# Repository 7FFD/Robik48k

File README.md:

# Robik48k

One of my collegues has sent to me ZX Robik, one of the ZX Spectrum clones created in SU.
During restoration, I've collected some artifacts that can be useful.

## AV-board-robik

The schematic of video output cascade to isolate logic from TV Set (SCART).
Indeed, Robik doen't have such cascade that in some cases leads to burning KP556PT2.
This schematic was borrowed from Harlequin.

## LM2596

Replacement of 7805 voltage regulator with more efficient based on LM2596.

## Robik2ZXBusAdapter

In order to connect ZX Spectrum pereferial to Robik an adapter has been created.
Besides that few changes on Robik must be applied, see Robik_Nick+fixed_by_Maksym_7FFD:
1. Make ROMCS signal working by adding 560 omh resistors
2. Add KJOYCS signal and connect to system connector
3. Fix /WAIT signal to work on input
4. Add +12V to system connector

## W27C512toKP556PT2

Since KP556PT2 is quite old IC with low reliability it's much better to replace with EEPROM W27C512-50.
Both D26/D27 can be replaced, use /xxxrom-dump/robik-plm-012-01-D26.bin for video output PLM and /xxxrom-dump/robik-plm-012-D27.bin for system PLM.

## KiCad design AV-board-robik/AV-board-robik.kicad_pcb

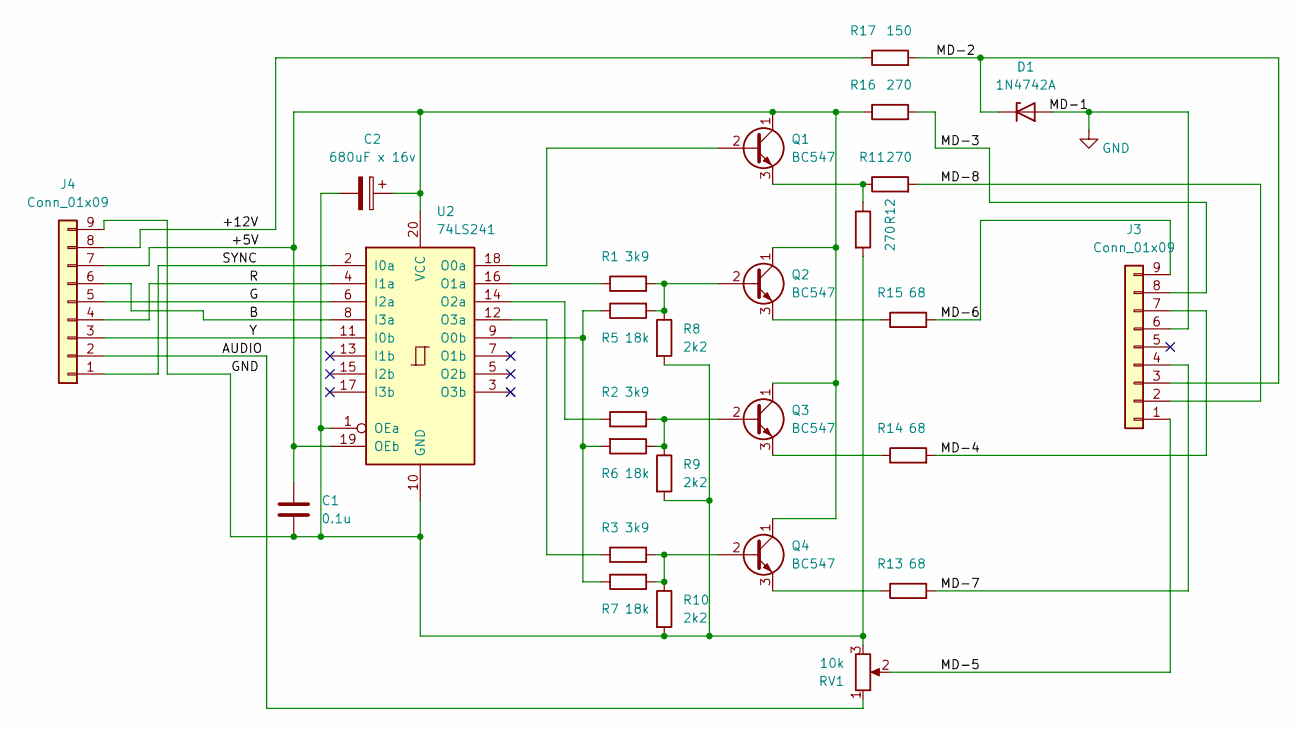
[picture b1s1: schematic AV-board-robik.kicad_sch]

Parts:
C1: 0.1u; C_Disc_D4.3mm_W1.9mm_P5.00mm
C2: 680uF x 16v; CP_Radial_D5.0mm_P2.50mm
D1: 1N4742A; D_DO-41_SOD81_P10.16mm_Horizontal
J3, J4: Conn_01x09; PinHeader_1x09_P2.54mm_Horizontal
Q1, Q2, Q3, Q4: BC547; TO-92_Inline
R1, R2, R3: 3k9; R_Axial_DIN0204_L3.6mm_D1.6mm_P5.08mm_Horizontal
R5, R6, R7: 18k; R_Axial_DIN0204_L3.6mm_D1.6mm_P5.08mm_Horizontal
R8, R9, R10: 2k2; R_Axial_DIN0204_L3.6mm_D1.6mm_P5.08mm_Horizontal
R11, R12, R16: 270; R_Axial_DIN0204_L3.6mm_D1.6mm_P5.08mm_Horizontal
R13, R14, R15: 68; R_Axial_DIN0204_L3.6mm_D1.6mm_P5.08mm_Horizontal
R17: 150; R_Axial_DIN0204_L3.6mm_D1.6mm_P5.08mm_Horizontal
RV1: 10k; Potentiometer_Piher_PT-6-V_Vertical
U2: 74LS241; DIP-20_W7.62mm_LongPads

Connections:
/+5V: C1.1, C2.1, J4.7, Q1.1 (C), Q2.1 (C), Q3.1 (C), Q4.1 (C), R16.1, U2.19 (OEb), U2.20 (VCC)
/+12V: J4.8, R17.1
/AUDIO: J4.2, RV1.1
/B: J4.6, U2.8 (I3a)
/G: J4.5, U2.6 (I2a)
/MD-2: D1.1 (K), J3.3, R17.2
/MD-3: J3.8, R16.2
/MD-4: J3.7, R14.2
/MD-5: J3.1, RV1.2
/MD-6: J3.9, R15.2
/MD-7: J3.4, R13.2
/MD-8: J3.2, R11.2
/R: J4.4, U2.4 (I1a)
/SYNC: J4.1, U2.2 (I0a)
/Y: J4.3, U2.11 (I0b)
GND: C1.2, C2.2, D1.2 (A), J3.6, J4.9, R8.2, R9.2, R10.2, R12.2, RV1.3, U2.1 (OEa), U2.10 (GND)
unnamed: Q1.2 (B), U2.18 (O0a)
unnamed: Q1.3 (E), R11.1, R12.1
unnamed: Q2.2 (B), R1.2, R5.2, R8.1
unnamed: Q2.3 (E), R15.1
unnamed: Q3.2 (B), R2.2, R6.1, R9.1
unnamed: Q3.3 (E), R14.1
unnamed: Q4.2 (B), R3.2, R7.2, R10.1
unnamed: Q4.3 (E), R13.1
unnamed: R5.1, R6.2, R7.1, U2.9 (O0b)
unnamed: R1.1, U2.16 (O1a)
unnamed: R2.1, U2.14 (O2a)
unnamed: R3.1, U2.12 (O3a)

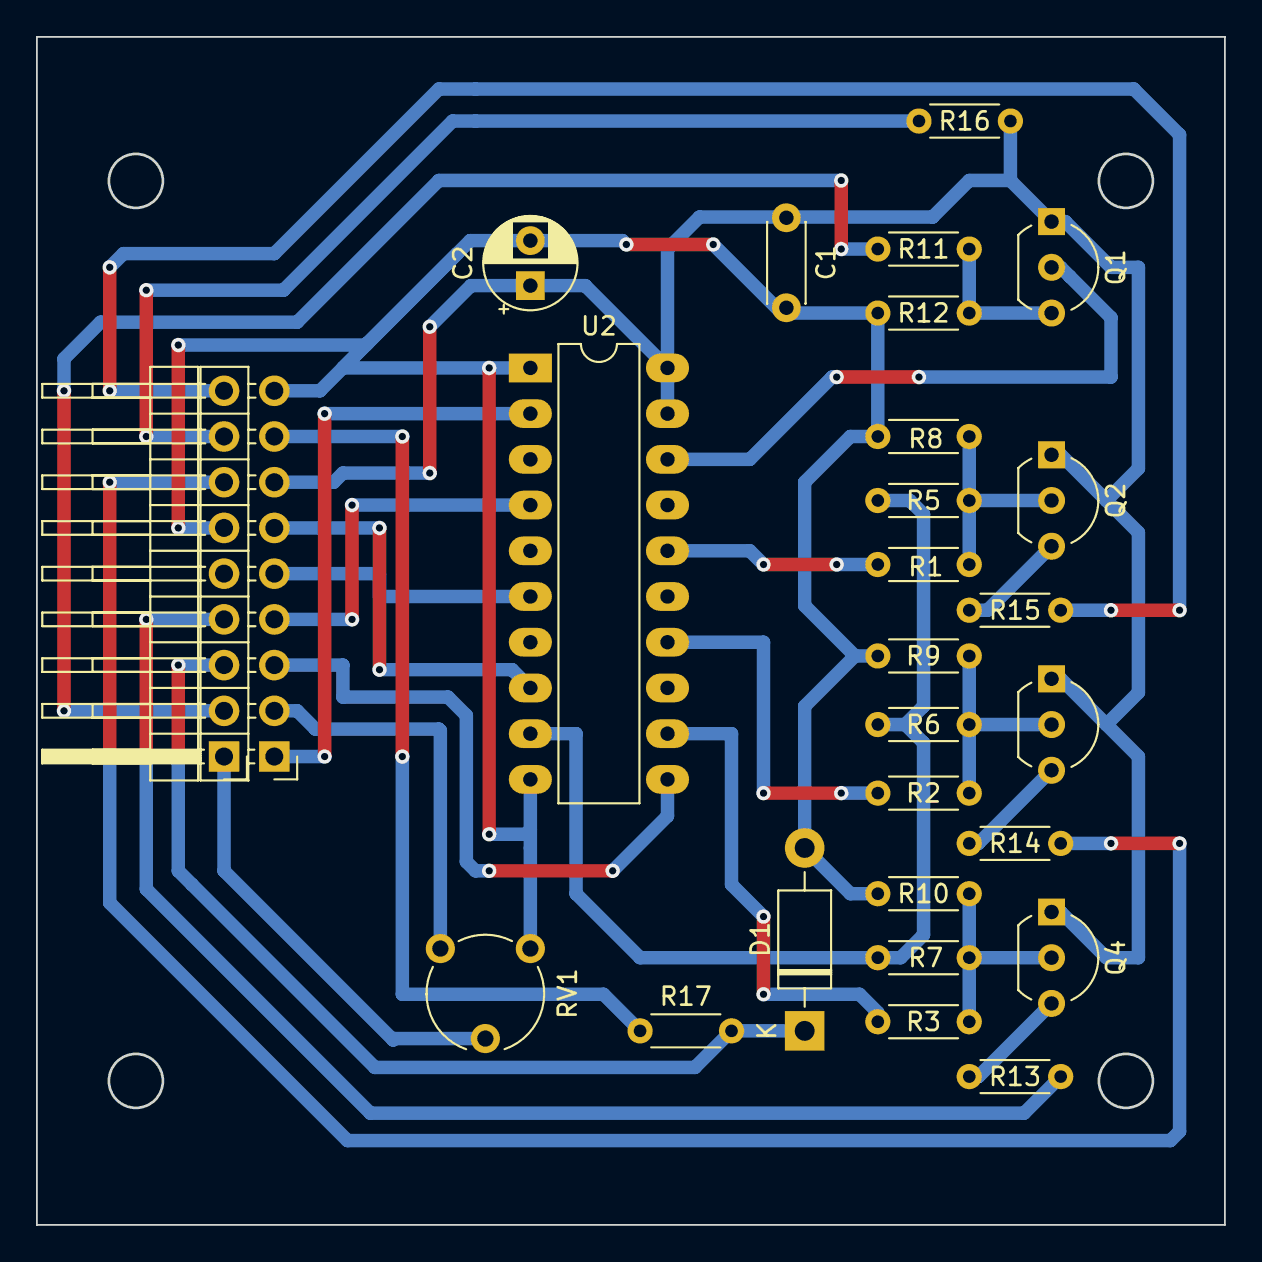
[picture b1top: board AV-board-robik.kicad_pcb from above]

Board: 2 copper layers, 66.0 x 66.0 mm, 27 parts (0 on the bottom side), 28 nets.

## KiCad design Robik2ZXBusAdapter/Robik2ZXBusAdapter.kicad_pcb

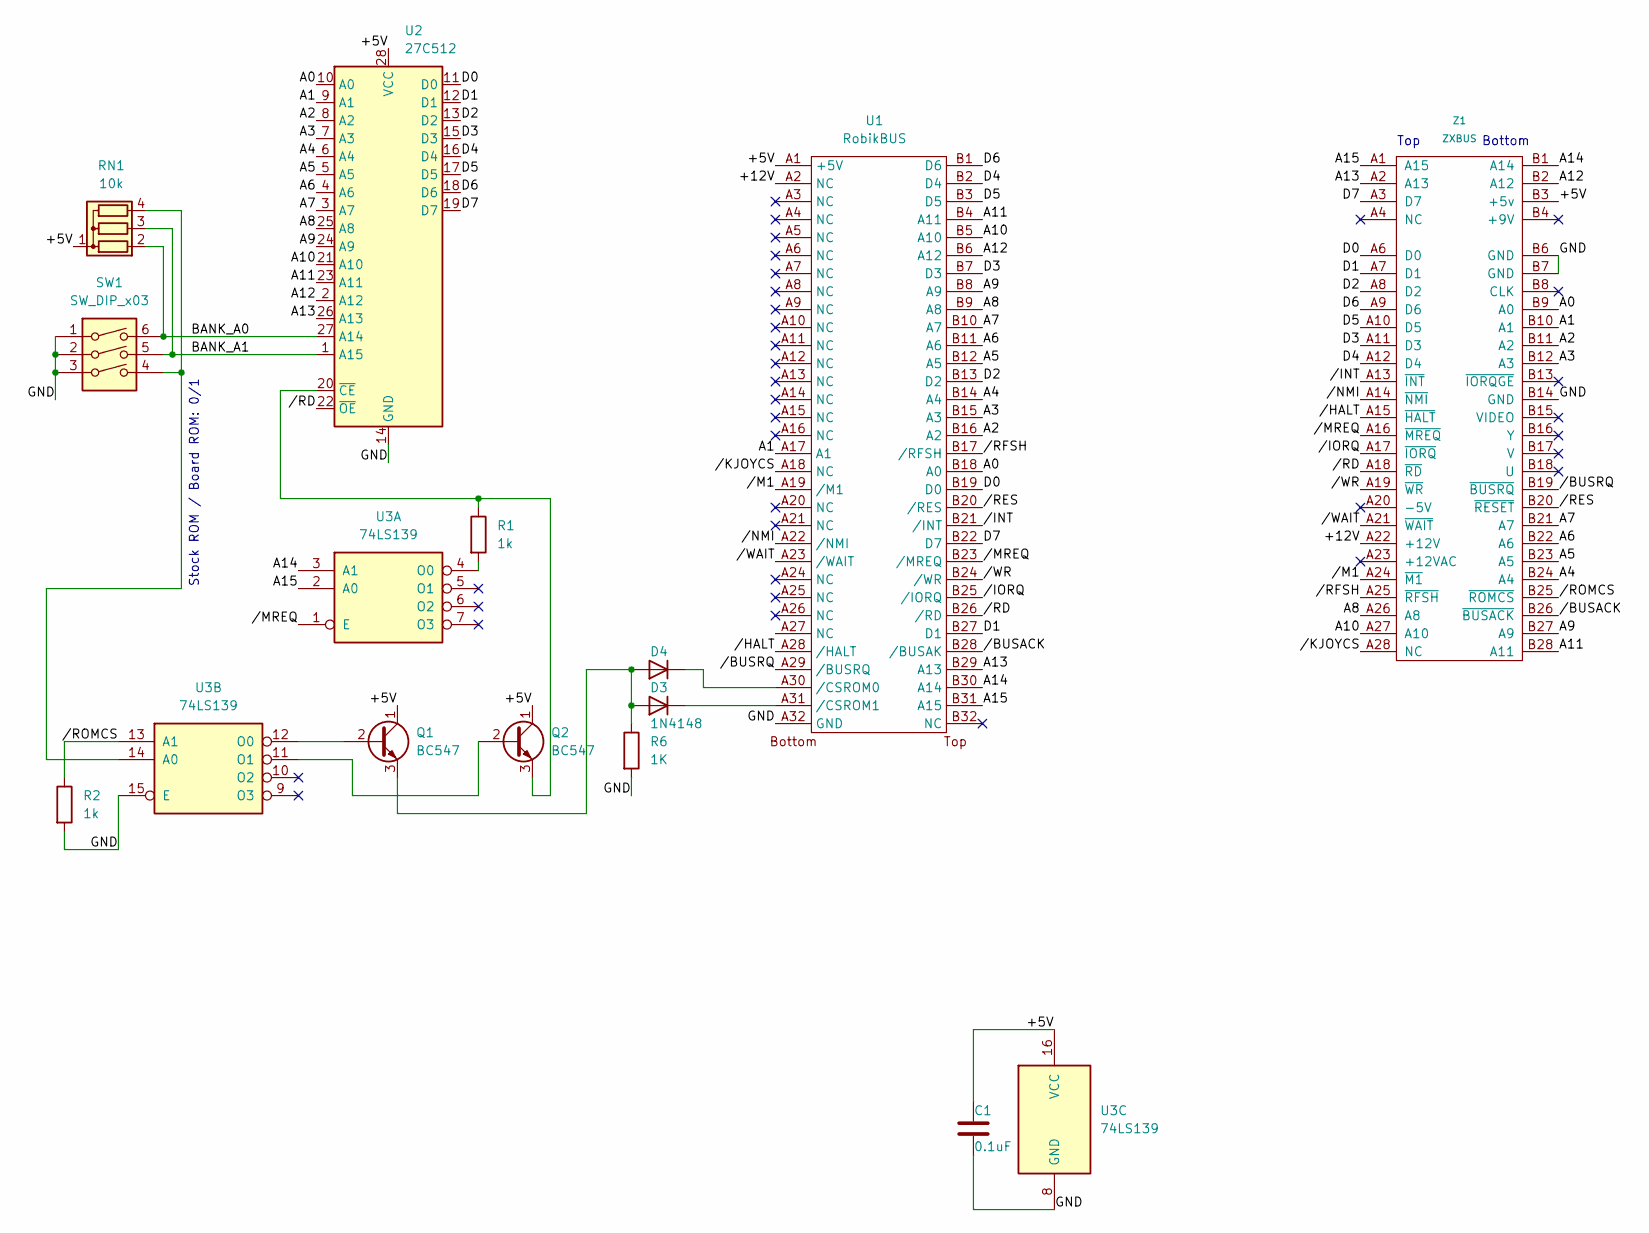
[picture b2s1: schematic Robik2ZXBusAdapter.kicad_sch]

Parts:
C1: 0.1uF; C_Disc_D4.7mm_W2.5mm_P5.00mm
D3, D4: 1N4148; D_DO-35_SOD27_P7.62mm_Horizontal
Q1, Q2: BC547; TO-92_Inline_Wide
R1, R2: 1k; R_Axial_DIN0204_L3.6mm_D1.6mm_P5.08mm_Vertical
R6: 1K; R_Axial_DIN0204_L3.6mm_D1.6mm_P5.08mm_Vertical
RN1: 10k; R_Array_SIP4
SW1: SW_DIP_x03; DIP-6_W7.62mm
U1: RobikBUS; RobikBUS_VERT
U2: 27C512; DIP-28_W15.24mm
U3: 74LS139; DIP-16_W7.62mm
Z1: ZXBUS

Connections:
/+5V: C1.1, Q1.1 (C), Q2.1 (C), RN1.1 (common), U1.A1 (+5V), U2.28 (VCC), U3.16 (VCC), Z1.B3 (+5v)
/+12V: U1.A2 (NC), Z1.A22 (+12V)
/A0: U1.B18 (A0), U2.10 (A0), Z1.B9 (A0)
/A1: U1.A17 (A1), U2.9 (A1), Z1.B10 (A1)
/A2: U1.B16 (A2), U2.8 (A2), Z1.B11 (A2)
/A3: U1.B15 (A3), U2.7 (A3), Z1.B12 (A3)
/A4: U1.B14 (A4), U2.6 (A4), Z1.B24 (A4)
/A5: U1.B12 (A5), U2.5 (A5), Z1.B23 (A5)
/A6: U1.B11 (A6), U2.4 (A6), Z1.B22 (A6)
/A7: U1.B10 (A7), U2.3 (A7), Z1.B21 (A7)
/A8: U1.B9 (A8), U2.25 (A8), Z1.A26 (A8)
/A9: U1.B8 (A9), U2.24 (A9), Z1.B27 (A9)
/A10: U1.B5 (A10), U2.21 (A10), Z1.A27 (A10)
/A11: U1.B4 (A11), U2.23 (A11), Z1.B28 (A11)
/A12: U1.B6 (A12), U2.2 (A12), Z1.B2 (A12)
/A13: U1.B29 (A13), U2.26 (A13), Z1.A2 (A13)
/A14: U1.B30 (A14), U3.3 (A1), Z1.B1 (A14)
/A15: U1.B31 (A15), U3.2 (A0), Z1.A1 (A15)
/BANK_A0: RN1.2 (R1), SW1.6, U2.27 (A14)
/BANK_A1: RN1.3 (R2), SW1.5, U2.1 (A15)
/D0: U1.B19 (D0), U2.11 (D0), Z1.A6 (D0)
/D1: U1.B27 (D1), U2.12 (D1), Z1.A7 (D1)
/D2: U1.B13 (D2), U2.13 (D2), Z1.A8 (D2)
/D3: U1.B7 (D3), U2.15 (D3), Z1.A11 (D3)
/D4: U1.B2 (D4), U2.16 (D4), Z1.A12 (D4)
/D5: U1.B3 (D5), U2.17 (D5), Z1.A10 (D5)
/D6: U1.B1 (D6), U2.18 (D6), Z1.A9 (D6)
/D7: U1.B22 (D7), U2.19 (D7), Z1.A3 (D7)
/GND: C1.2, R2.2, R6.2, SW1.1, SW1.2, SW1.3, U1.A32 (GND), U2.14 (GND), U3.8 (GND), U3.15 (E), Z1.B6 (GND), Z1.B7 (GND), Z1.B14 (GND)
//BUSACK: U1.B28 (/BUSAK), Z1.B26 (~BUSACK)
//BUSRQ: U1.A29 (/BUSRQ), Z1.B19 (~BUSRQ)
//HALT: U1.A28 (/HALT), Z1.A15 (~HALT)
//INT: U1.B21 (/INT), Z1.A13 (~INT)
//IORQ: U1.B25 (/IORQ), Z1.A17 (~IORQ)
//KJOYCS: U1.A18 (NC), Z1.A28 (NC)
//M1: U1.A19 (/M1), Z1.A24 (~M1)
//MREQ: U1.B23 (/MREQ), U3.1 (E), Z1.A16 (~MREQ)
//NMI: U1.A22 (/NMI), Z1.A14 (~NMI)
//RD: U1.B26 (/RD), U2.22 (~OE), Z1.A18 (~RD)
//RES: U1.B20 (/RES), Z1.B20 (~RESET)
//RFSH: U1.B17 (/RFSH), Z1.A25 (~RFSH)
//ROMCS: R2.1, U3.13 (A1), Z1.B25 (~ROMCS)
//WAIT: U1.A23 (/WAIT), Z1.A21 (~WAIT)
//WR: U1.B24 (/WR), Z1.A19 (~WR)
unnamed: D3.2 (A), D4.2 (A), Q1.3 (E), R6.1
unnamed: D3.1 (K), U1.A31 (/CSROM1)
unnamed: D4.1 (K), U1.A30 (/CSROM0)
unnamed: Q1.2 (B), U3.12 (O0)
unnamed: Q2.2 (B), U3.11 (O1)
unnamed: Q2.3 (E), R1.1, U2.20 (~CE)
unnamed: RN1.4 (R3), SW1.4, U3.14 (A0)
unnamed: R1.2, U3.4 (O0)

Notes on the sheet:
Stock ROM / Board ROM: 0/1
Top Bottom

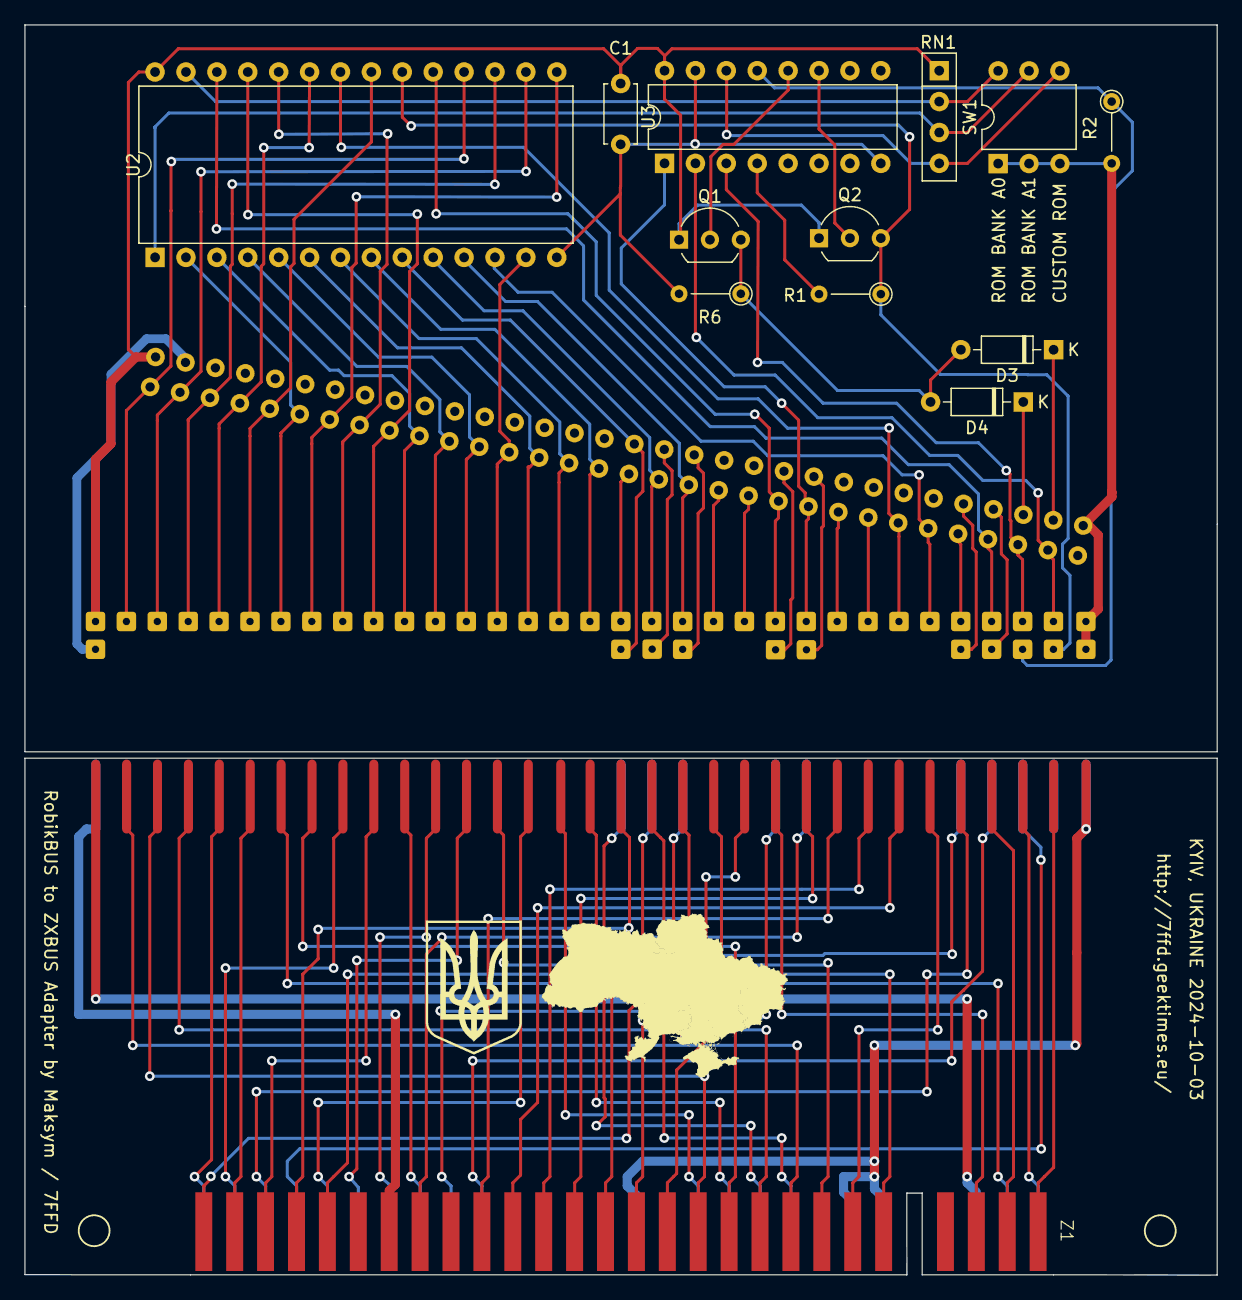
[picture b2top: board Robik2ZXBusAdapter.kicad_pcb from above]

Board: 2 copper layers, 98.0 x 102.8 mm, 16 parts (1 on the bottom side), 52 nets.

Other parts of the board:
MAP: UA CoA 21x14mm; UA map 21x14mm Silk
UA CoA: UA CoA 8x11mm

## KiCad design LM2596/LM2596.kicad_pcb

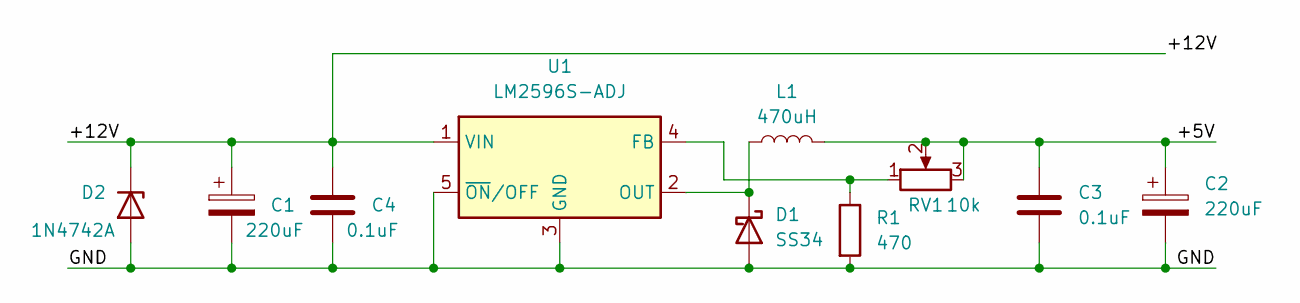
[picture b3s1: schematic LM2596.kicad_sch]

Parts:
C1, C2: 220uF; CP_Radial_D7.5mm_P2.50mm
C3, C4: 0.1uF; C_Disc_D3.8mm_W2.6mm_P2.50mm
D1: SS34; D_DO-27_P15.24mm_Horizontal
D2: 1N4742A; D_DO-41_SOD81_P10.16mm_Horizontal
L1: 470uH; L_Radial_D8.7mm_P5.00mm_Fastron_07HCP
R1: 470; R_Axial_DIN0204_L3.6mm_D1.6mm_P5.08mm_Horizontal
RV1: 10k; Potentiometer_Vishay_T73XW_Horizontal
U1: LM2596S-ADJ; TO-220F-5_P3.4x2.06mm_StaggerOdd_Lead1.86mm_Vertical

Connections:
/+5V: C2.1, C3.1, L1.2, RV1.2, RV1.3
/+12V: C1.1, C4.1, D2.1 (K), U1.1 (VIN)
/GND: C1.2, C2.2, C3.2, C4.2, D1.2 (A), D2.2 (A), R1.2, U1.3 (GND), U1.5 (~ON/OFF)
unnamed: D1.1 (K), L1.1, U1.2 (OUT)
unnamed: R1.1, RV1.1, U1.4 (FB)

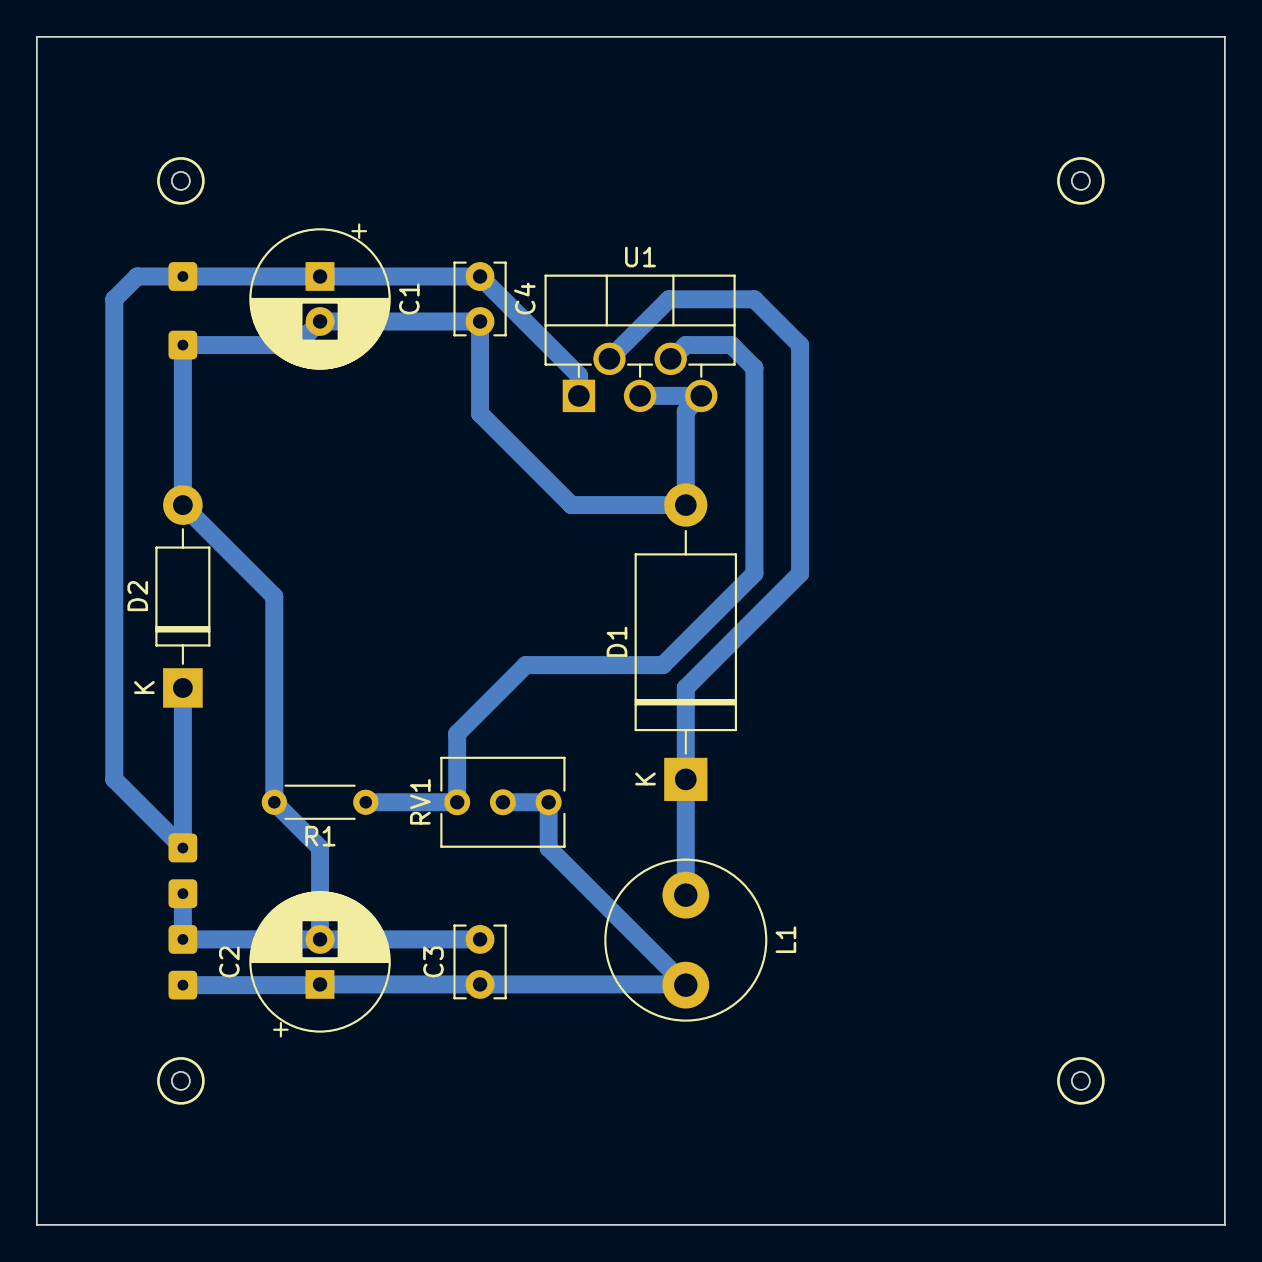
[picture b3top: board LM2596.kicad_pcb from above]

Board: 2 copper layers, 66.0 x 66.0 mm, 10 parts (0 on the bottom side), 5 nets.

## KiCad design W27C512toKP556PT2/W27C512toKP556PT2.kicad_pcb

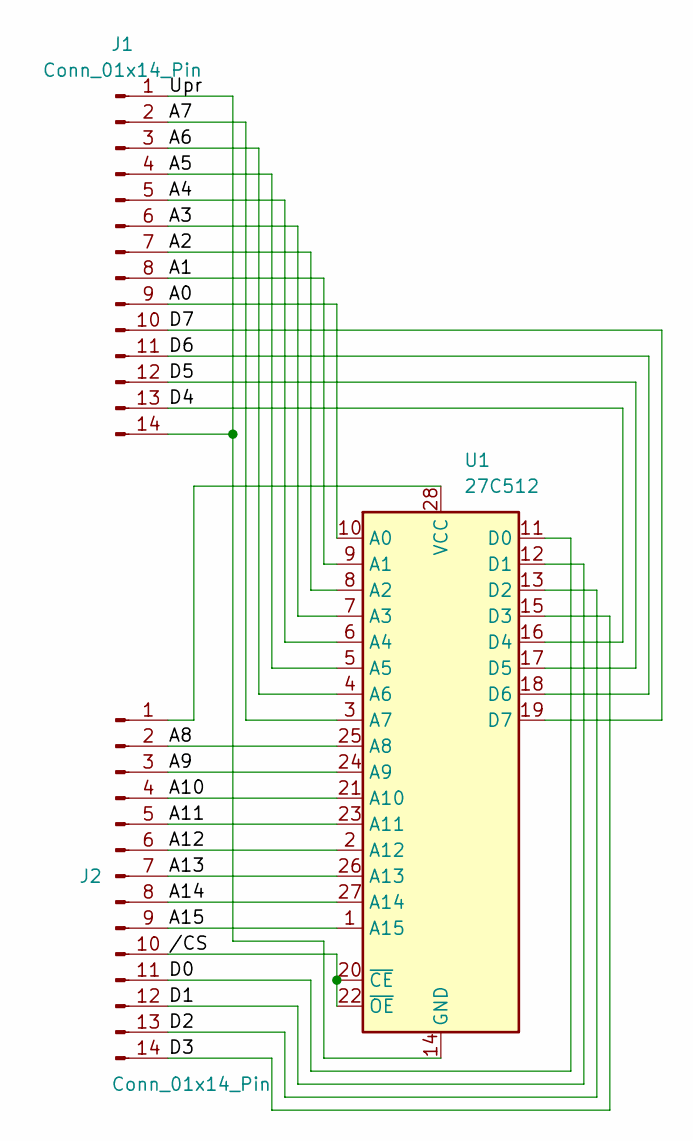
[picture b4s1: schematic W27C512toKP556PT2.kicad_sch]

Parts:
J1, J2: Conn_01x14_Pin; PinHeader_1x14_P2.54mm_Vertical
U1: 27C512; DIP-28_W15.24mm

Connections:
/A0: J1.9, U1.10 (A0)
/A1: J1.8, U1.9 (A1)
/A2: J1.7, U1.8 (A2)
/A3: J1.6, U1.7 (A3)
/A4: J1.5, U1.6 (A4)
/A5: J1.4, U1.5 (A5)
/A6: J1.3, U1.4 (A6)
/A7: J1.2, U1.3 (A7)
/A8: J2.2, U1.25 (A8)
/A9: J2.3, U1.24 (A9)
/A10: J2.4, U1.21 (A10)
/A11: J2.5, U1.23 (A11)
/A12: J2.6, U1.2 (A12)
/A13: J2.7, U1.26 (A13)
/A14: J2.8, U1.27 (A14)
/A15: J2.9, U1.1 (A15)
/D0: J2.11, U1.11 (D0)
/D1: J2.12, U1.12 (D1)
/D2: J2.13, U1.13 (D2)
/D3: J2.14, U1.15 (D3)
/D4: J1.13, U1.16 (D4)
/D5: J1.12, U1.17 (D5)
/D6: J1.11, U1.18 (D6)
/D7: J1.10, U1.19 (D7)
/Upr: J1.1, J1.14, U1.14 (GND)
//CS: J2.10, U1.20 (~CE), U1.22 (~OE)
unnamed: J2.1, U1.28 (VCC)

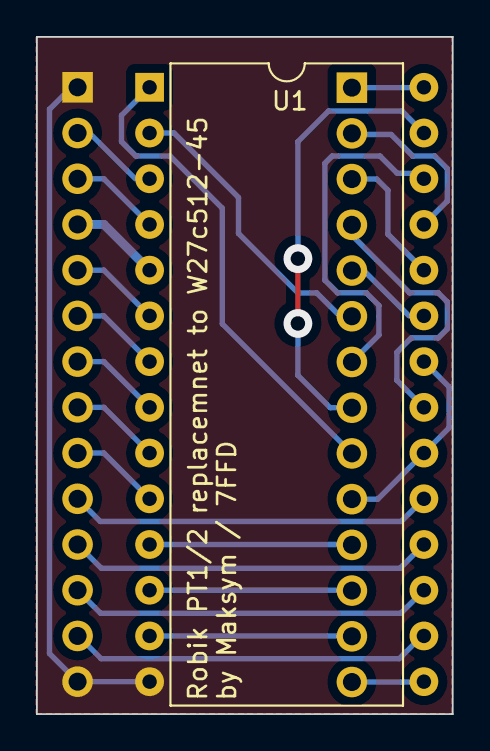
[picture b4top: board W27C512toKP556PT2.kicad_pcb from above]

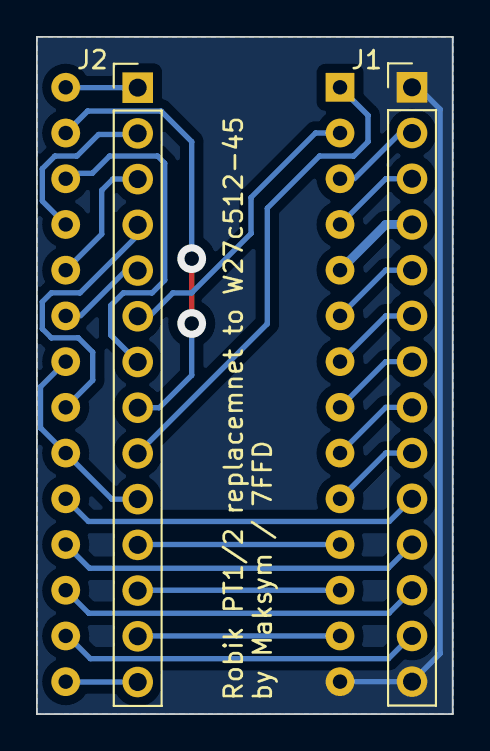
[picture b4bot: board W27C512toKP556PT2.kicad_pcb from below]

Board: 2 copper layers, 23.1 x 37.6 mm, 3 parts (2 on the bottom side), 27 nets.

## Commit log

2024-10-27 Video PT timings
2024-10-27 patched UA charset and banner
2024-10-27 added robik documentation and firmwares
2024-10-27 lm2596 schematic and board
2024-10-27 fixed av-board issues
2024-10-27 fixed issues
2024-10-27 KP556PT2 replacement to W27C512-45
2024-10-27 Initial commit for replacement board
2024-10-27 Robik documentation
2024-10-27 AudioVideo board like Harlequin for any ZX Clone
2024-10-27 Added capacitor to smooth interference
2024-10-27 Robik to ZXBUS adapter
2024-10-27 added joistick /cs
2024-10-27 finished board
2024-10-27 added FDD connector adapter for FDD cable
2024-10-27 changed /csjoy signal to A18
2024-10-27 pcb2gcode script
2024-10-27 rom2ram switch code
2024-10-27 dumps moved to folder
2024-10-27 the root cause of STS issue has been found added code to switch from rom to ram with basic copy
2024-10-27 reorg dumps folders
2024-10-27 changed settings for pcb2gcode for specific board
2024-10-27 robik bus changes
2024-10-27 applied fixes for pull-up resistors
2024-10-27 fixed resistor on cs joystick and moved to A18 from A27
2024-10-27 is used only for development purpose because pathched symbols cause isssue with STS
2024-10-27 forked av-board with board design for robik
2024-10-27 added optional rom selector to adapter
2024-10-27 Fixed schematic
2024-10-27 remane schematic
2024-10-27 added /WAIT fix on Robik
2025-07-10 Aligned resistors values for usage with 74LS logic that improves color brightness
2025-07-10 Updated ROMS for adapter
